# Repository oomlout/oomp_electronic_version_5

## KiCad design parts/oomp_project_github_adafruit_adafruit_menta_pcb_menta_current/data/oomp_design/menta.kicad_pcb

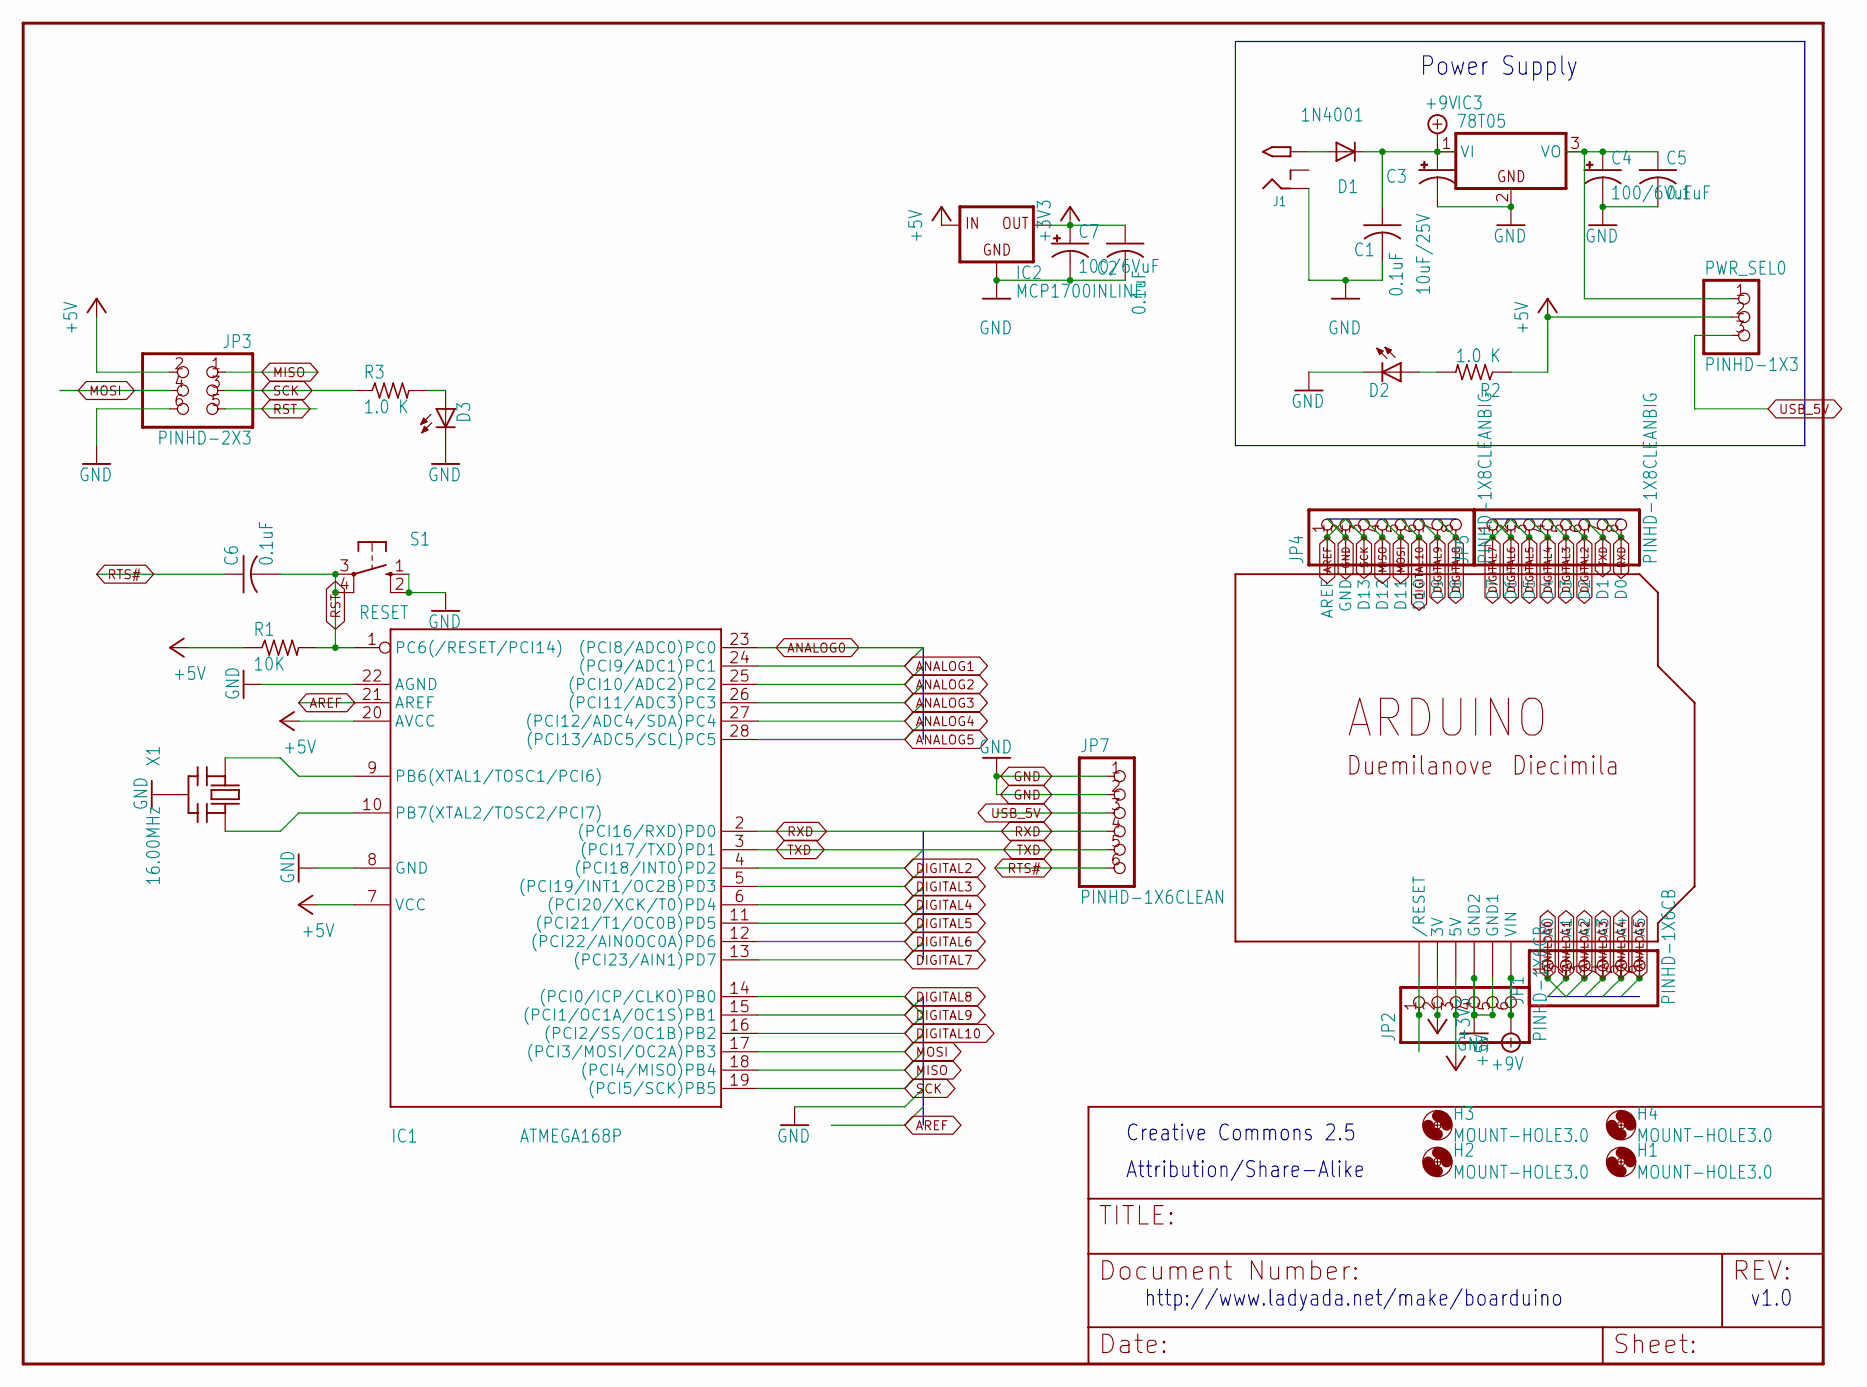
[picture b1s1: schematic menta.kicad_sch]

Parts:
C1, C2, C5, C6: 0.1uF; C025-025X050
C3: 10uF/25V; E2,5-6
C4, C7: 100/6VuF; E2,5-6
D1: 1N4001; DO41-10
D2: LED3MM
D3: Green; LED3MM
H1, H2, H3, H4: MOUNT-HOLE3.0; 3,0
IC1: ATMEGA168P; DIL28_3
IC2: MCP1700INLINE; TO92-INLINE
IC3: 78T05; TO220H
J1: 2.1MMJACK; PJ-102A
JP1, JP2: PINHD-1X6CB; 1X06-CLEANBIG
JP3: PINHD-2X3; 2X03
JP4, JP5: PINHD-1X8CLEANBIG; 1X08-CLEANBIG
JP7: PINHD-1X6CLEAN; 1X06-CLEAN
PWR_SEL0: PINHD-1X3; 1X03
R1: 10K; 0207_10
R2, R3: 1.0 K; 0207_10
S1: RESET; B3F-10XX
U$2: ARDUINO-NOHOLE
X1: 16.00MHz; CERM_OSC

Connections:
+3V3: C2.1, C7.+, IC2.3 (OUT), JP2.2, U$2.3V
+5V: IC1.7 (VCC), IC1.20 (AVCC), IC2.2 (IN), JP2.3, JP3.2, PWR_SEL0.2, R1.1, R2.1, U$2.5V
+9V: C1.1, C3.+, D1.C, IC3.1 (VI), JP2.6, U$2.VIN
ANALOG0: IC1.23 ((PCI8/ADC0)PC0), JP1.1, U$2.A0
ANALOG1: IC1.24 ((PCI9/ADC1)PC1), JP1.2, U$2.A1
ANALOG2: IC1.25 ((PCI10/ADC2)PC2), JP1.3, U$2.A2
ANALOG3: IC1.26 ((PCI11/ADC3)PC3), JP1.4, U$2.A3
ANALOG4: IC1.27 ((PCI12/ADC4/SDA)PC4), JP1.5, U$2.A4
ANALOG5: IC1.28 ((PCI13/ADC5/SCL)PC5), JP1.6, U$2.A5
AREF: IC1.21 (AREF), JP4.1, U$2.AREF
DIGITAL2: IC1.4 ((PCI18/INT0)PD2), JP5.6, U$2.D2
DIGITAL3: IC1.5 ((PCI19/INT1/OC2B)PD3), JP5.5, U$2.D3
DIGITAL4: IC1.6 ((PCI20/XCK/T0)PD4), JP5.4, U$2.D4
DIGITAL5: IC1.11 ((PCI21/T1/OC0B)PD5), JP5.3, U$2.D5
DIGITAL6: IC1.12 ((PCI22/AIN0OC0A)PD6), JP5.2, U$2.D6
DIGITAL7: IC1.13 ((PCI23/AIN1)PD7), JP5.1, U$2.D7
DIGITAL8: IC1.14 ((PCI0/ICP/CLKO)PB0), JP4.8, U$2.D8
DIGITAL9: IC1.15 ((PCI1/OC1A/OC1S)PB1), JP4.7, U$2.D9
DIGITAL10: IC1.16 ((PCI2/SS/OC1B)PB2), JP4.6, U$2.D10
GND: C1.2, C2.2, C3.-, C4.-, C5.2, C7.-, D2.K (C), D3.K (C), IC1.8 (GND), IC1.22 (AGND), IC2.1 (GND), IC3.2 (GND), J1.RING, JP2.4, JP2.5, JP3.6, JP4.2, JP7.1, JP7.2, S1.1 (S), S1.2 (S1), U$2.GND, U$2.GND1, U$2.GND2, X1.P$2 (GND)
MISO: IC1.18 ((PCI4/MISO)PB4), JP3.1, JP4.4, U$2.D12
MOSI: IC1.17 ((PCI3/MOSI/OC2A)PB3), JP3.4, JP4.5, U$2.D11
unnamed: IC1.9 (PB6(XTAL1/TOSC1/PCI6)), X1.P$1 (IN)
unnamed: IC1.10 (PB7(XTAL2/TOSC2/PCI7)), X1.P$3 (OUT)
unnamed: D2.A, R2.2
unnamed: D3.A, R3.2
unnamed: C4.+, C5.1, IC3.3 (VO), PWR_SEL0.1
unnamed: D1.A, J1.TIP
RTS#: C6.1, JP7.6
RXD: IC1.2 ((PCI16/RXD)PD0), JP5.8, JP7.4, U$2.D0
SCK: IC1.19 ((PCI5/SCK)PB5), JP3.3, JP4.3, R3.1, U$2.D13
TXD: IC1.3 ((PCI17/TXD)PD1), JP5.7, JP7.5, U$2.D1
USB_5V: JP7.3, PWR_SEL0.3

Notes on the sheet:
Power Supply
v1.0
http://www.ladyada.net/make/boarduino
Attribution/Share-Alike
Creative Commons 2.5

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
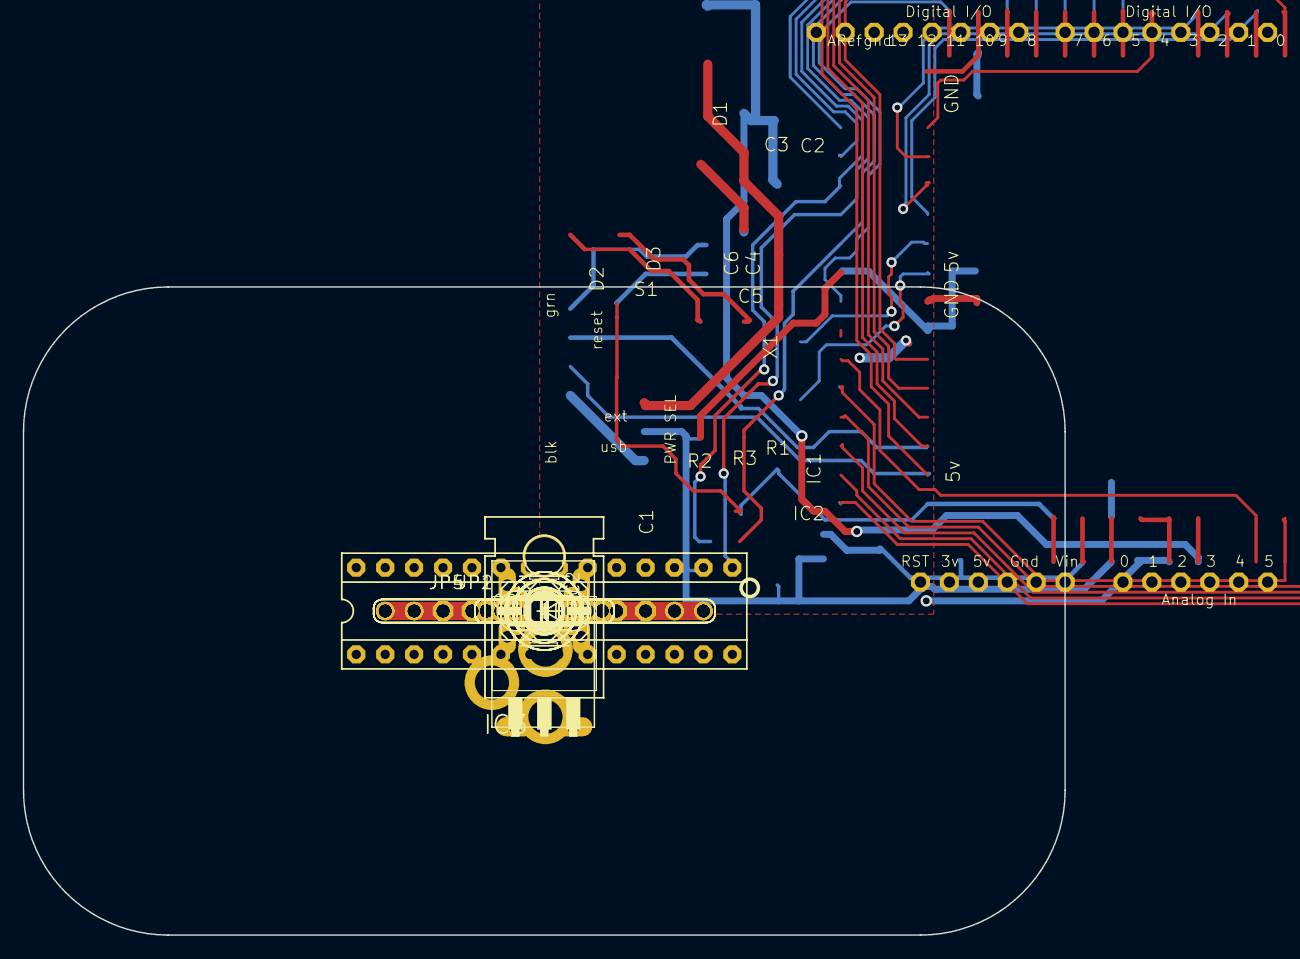
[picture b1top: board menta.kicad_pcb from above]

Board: 16 copper layers, 91.4 x 56.9 mm, 60 parts (1 on the bottom side), 34 nets.

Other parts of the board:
U$3, U$4, U$5, U$6: 12-STRIP
U$7, U$8, U$9, U$10, U$11, U$12, U$13, U$14, U$15, U$16, U$17, U$18, U$19, U$20, U$21, U$22, U$23, U$24, U$25, U$26, U$27, U$28, U$29, U$30: 5-STRIP
U$31: ALTOIDSTIN-DIM

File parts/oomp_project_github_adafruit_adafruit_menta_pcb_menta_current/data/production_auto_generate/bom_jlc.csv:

Comment,Designator,Footprint,LCSC Part #
,PWR_SEL0,menta-import-fps:1X03,C49257
,JP7,menta-import-fps:1X06-CLEAN,C37208
,"JP1,JP2",menta-import-fps:1X06-CLEANBIG,C37208
,"JP4,JP5",menta-import-fps:1X08-CLEANBIG,C492421
,JP3,menta-import-fps:2X03,
,U$31,menta-import-fps:ALTOIDSTIN-DIM,
,D2,menta-import-fps:LED3MM,
,IC2,menta-import-fps:TO92-INLINE,
0.1uF,"C1,C2,C5,C6",menta-import-fps:C025-025X050,
1.0 K,"R2,R3",menta-import-fps:0207_10,
100/6VuF,"C4,C7","menta-import-fps:E2,5-6",
10K,R1,menta-import-fps:0207_10,
10uF/25V,C3,"menta-import-fps:E2,5-6",
1N4001,D1,menta-import-fps:DO41-10,
2.1MMJACK,J1,menta-import-fps:PJ-102A,
7805T,IC3,menta-import-fps:TO220H,
ARDUINO-NOHOLE,U$2,menta-import-fps:ARDUINO-NOHOLE,
ATMEGA168P,IC1,menta-import-fps:DIL28_3,
Green,D3,menta-import-fps:LED3MM,
RESET,S1,menta-import-fps:B3F-10XX,

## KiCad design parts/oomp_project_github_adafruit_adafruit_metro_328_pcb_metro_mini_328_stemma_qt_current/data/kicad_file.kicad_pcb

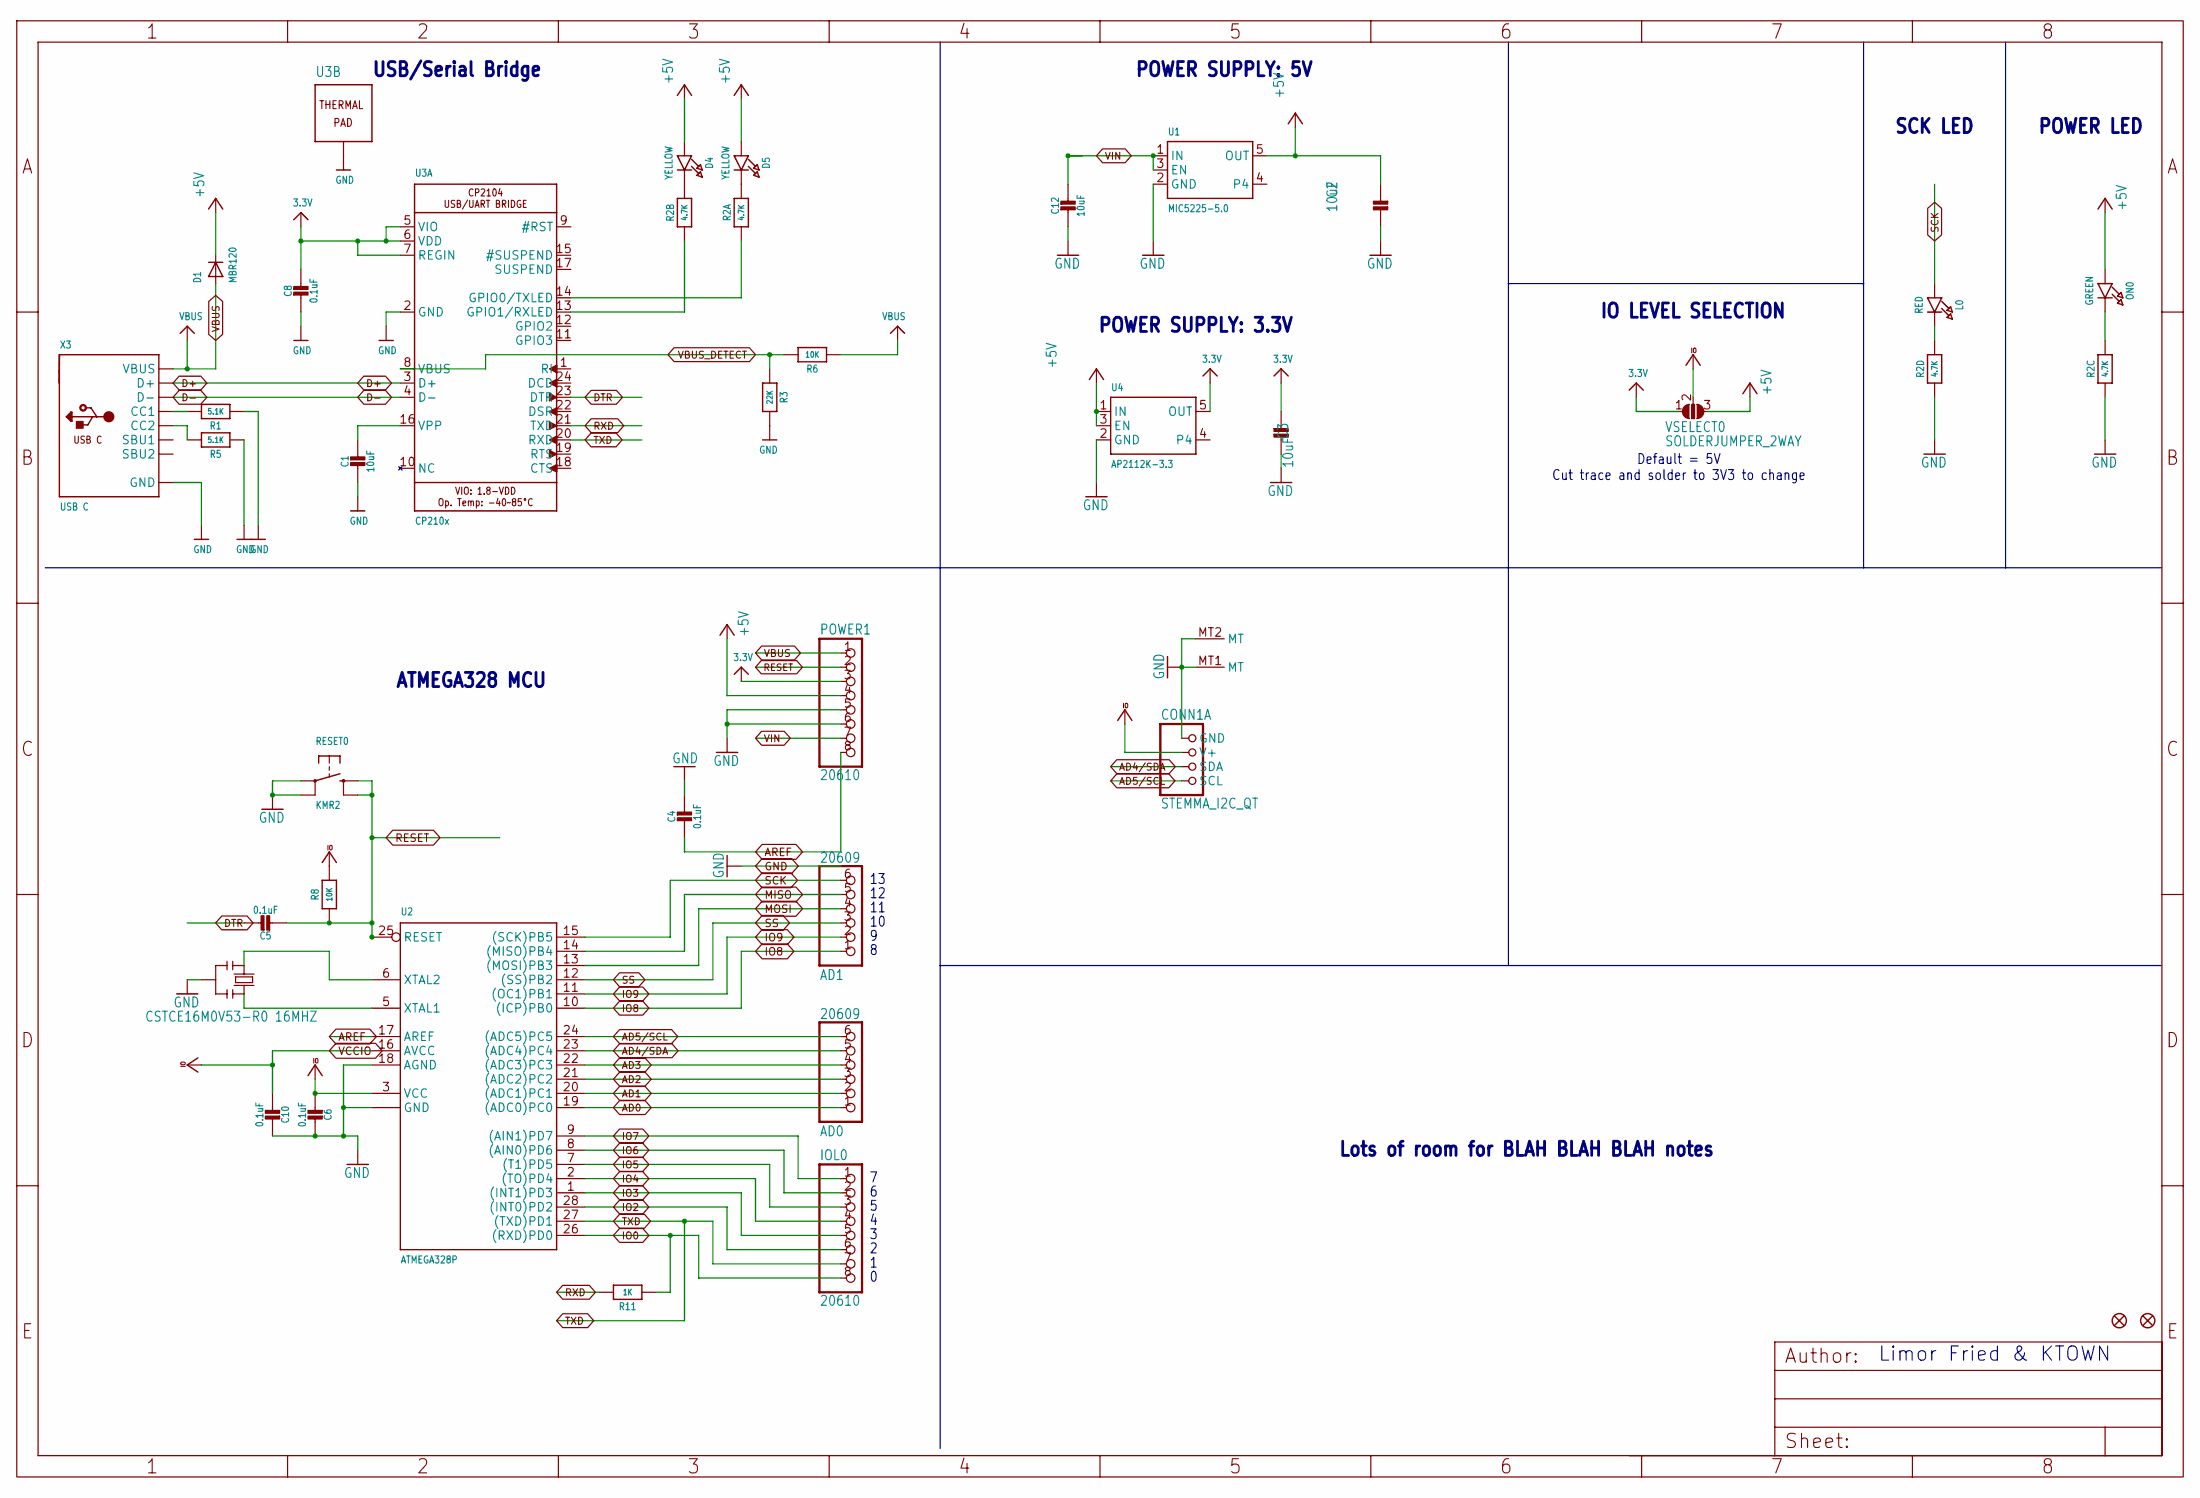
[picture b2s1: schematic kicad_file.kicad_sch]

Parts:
AD0, AD1: 20609; 1X06_ROUND
C1, C2, C3, C12: 10uF; 0805-NO
C4, C5, C6, C8, C10: 0.1uF; 0603-NO
CONN1: STEMMA_I2C_QT; JST_SH4
D1: MBR120; SOD-123FL
D4, D5: YELLOW; CHIPLED_0603_NOOUTLINE
FD1, FD2: FIDUCIAL_1MM
IOL0: 20610; 1X08_ROUND
L0: RED; CHIPLED_0603_NOOUTLINE
ON0: GREEN; CHIPLED_0603_NOOUTLINE
POWER1: 20610; 1X08_ROUND_70
R1, R5: 5.1K; 0603-NO
R2: 4.7K; RESPACK_4X0603
R3: 22K; 0603-NO
R6, R8: 10K; 0603-NO
R11: 1K; 0603-NO
RESET0: KMR2; BTN_KMR2_4.6X2.8
U1: MIC5225-5.0; SOT23-5
U2: ATMEGA328P; QFN28_4MM_.45MM
U3: CP210x; QFN24_4MM_SMSC
U4: AP2112K-3.3; SOT23-5
VSELECT0: SOLDERJUMPER_2WAY; SOLDERJUMPER_2WAY_OPEN_NOPASTE
X3: USB C; USB_C_CUSB31-CFM2AX-01-X
Y2: CSTCE16M0V53-R0 16MHZ; RESONATOR

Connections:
3.3V: C3.2, C8.1, POWER1.3, U3.5 (VIO), U3.6 (VDD), U3.7 (REGIN), U4.5 (OUT), VSELECT0.1
+5V: C2.2, D1.C, D4.A, D5.A, ON0.A, POWER1.4, U1.5 (OUT), U4.1 (IN), U4.3 (EN), VSELECT0.3
AD0: AD0.1, U2.19 ((ADC0)PC0)
AD1: AD0.2, U2.20 ((ADC1)PC1)
AD2: AD0.3, U2.21 ((ADC2)PC2)
AD3: AD0.4, U2.22 ((ADC3)PC3)
AD4/SDA: AD0.5, CONN1.3 (SDA), U2.23 ((ADC4)PC4)
AD5/SCL: AD0.6, CONN1.4 (SCL), U2.24 ((ADC5)PC5)
AREF: C4.2, POWER1.8, U2.17 (AREF)
D+: U3.3 (D+), X3.A6 (D+), X3.B6 (D+)
D-: U3.4 (D-), X3.A7 (D-), X3.B7 (D-)
DTR: C5.1, U3.23 (DTR)
GND: C1.2, C2.1, C3.1, C4.1, C6.1, C8.2, C10.1, C12.2, CONN1.1 (GND), CONN1.MT1 (MT), CONN1.MT2 (MT), POWER1.5, POWER1.6, R1.1, R2.3 (1), R2.4 (1), R3.1, R5.1, RESET0.A, RESET0.A' (P1), U1.2 (GND), U2.4 (GND), U2.18 (AGND), U2.29 (GND), U3.2 (GND), U3.THERM (TP), U4.2 (GND), X3.A1B12 (GND), X3.B1A12 (GND), Y2.2
IO0: IOL0.8, R11.1, U2.26 ((RXD)PD0)
IO2: IOL0.6, U2.28 ((INT0)PD2)
IO3: IOL0.5, U2.1 ((INT1)PD3)
IO4: IOL0.4, U2.2 ((TO)PD4)
IO5: IOL0.3, U2.7 ((T1)PD5)
IO6: IOL0.2, U2.8 ((AIN0)PD6)
IO7: IOL0.1, U2.9 ((AIN1)PD7)
IO8: AD1.1, U2.10 ((ICP)PB0)
IO9: AD1.2, U2.11 ((OC1)PB1)
MISO: AD1.5, U2.14 ((MISO)PB4)
MOSI: AD1.4, U2.13 ((MOSI)PB3)
unnamed: L0.C, R2.5 (2)
unnamed: ON0.C, R2.6 (2)
unnamed: R2.1, U3.14 (GPIO0/TXLED)
unnamed: R1.2, X3.A5 (CC1)
unnamed: D4.C, R2.7 (2)
unnamed: D5.C, R2.8 (2)
unnamed: R5.2, X3.B5 (CC2)
unnamed: C1.1, U3.16 (VPP)
unnamed: R2.2 (1), U3.13 (GPIO1/RXLED)
RESET: C5.2, POWER1.2, R8.1, RESET0.B (S), RESET0.B' (S1), U2.25 (RESET)
RXD: R11.2, U3.21 (TXD)
SCK: AD1.6, L0.A, U2.15 ((SCK)PB5)
SS: AD1.3, U2.12 ((SS)PB2)
TXD: IOL0.7, U2.27 ((TXD)PD1), U3.20 (RXD)
VBUS: D1.A, POWER1.1, R6.2, X3.A4B9 (VBUS), X3.B4A9 (VBUS)
VBUS_DETECT: R3.2, R6.1, U3.8 (VBUS)
VCCIO: C6.2, C10.2, CONN1.2 (V+), R8.2, U2.3 (VCC), U2.16 (AVCC), VSELECT0.2
VIN: C12.1, POWER1.7, U1.1 (IN), U1.3 (EN)
XTAL1: U2.5 (XTAL1), Y2.3
XTAL2: U2.6 (XTAL2), Y2.1

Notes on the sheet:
POWER SUPPLY: 5V
SCK LED
POWER LED
Lots of room for BLAH BLAH BLAH notes
Limor Fried & KTOWN
Default = 5V Cut trace and solder to 3V3 to change
USB/Serial Bridge
IO LEVEL SELECTION
ATMEGA328 MCU
POWER SUPPLY: 3.3V

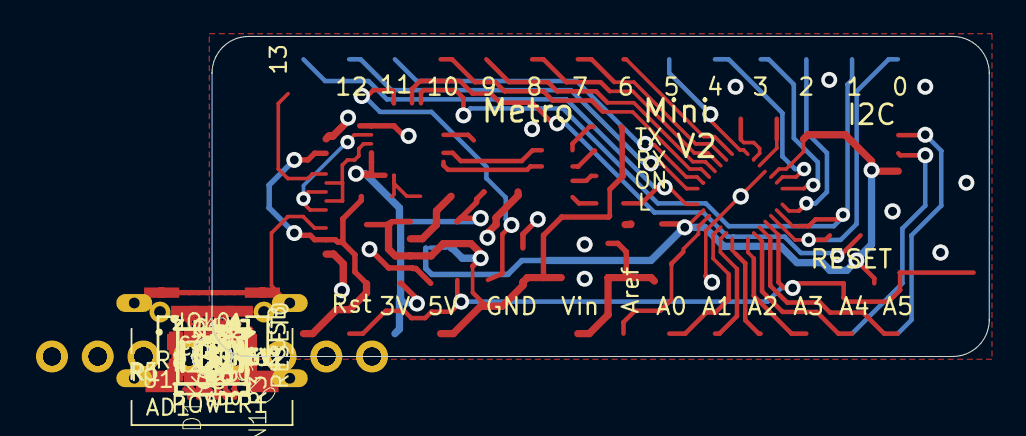
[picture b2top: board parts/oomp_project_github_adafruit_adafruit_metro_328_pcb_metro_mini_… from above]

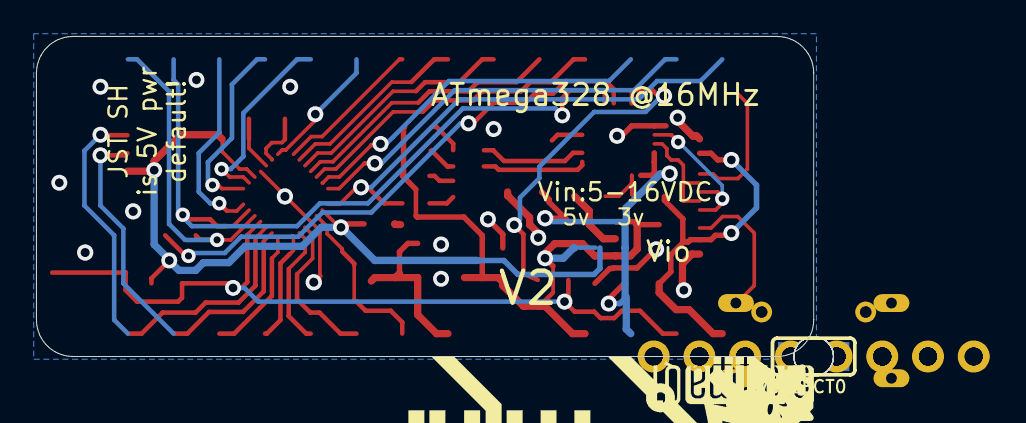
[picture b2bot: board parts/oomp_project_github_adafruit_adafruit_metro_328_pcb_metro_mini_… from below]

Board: 2 copper layers, 43.2 x 17.8 mm, 45 parts (4 on the bottom side), 44 nets.

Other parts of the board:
U$4: PCBFEAT-REV-040
U$5: ADAFRUIT_2.5MM
U$6: STEMMAQT
U$7: METROMINI_SILK
U$10: ADAFRUIT_5MM
UNK_HOLE_0: dummyfp0
UNK_HOLE_1: dummyfp1
UNK_HOLE_2: dummyfp2
UNK_HOLE_3: dummyfp3

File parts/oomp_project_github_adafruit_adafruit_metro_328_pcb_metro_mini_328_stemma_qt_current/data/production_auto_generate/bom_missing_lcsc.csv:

Designator,Comment,Footprint,OOMP ID,Reason
C1,10uF,Metro Mini 328 V2 - STEMMA QT-import-fps:0805-NO,electronic_capacitor_0805_10_micro_farad,No verified LCSC part number
C2,10uF,Metro Mini 328 V2 - STEMMA QT-import-fps:0805-NO,electronic_capacitor_0805_10_micro_farad,No verified LCSC part number
C3,10uF,Metro Mini 328 V2 - STEMMA QT-import-fps:0805-NO,electronic_capacitor_0805_10_micro_farad,No verified LCSC part number
C12,10uF,Metro Mini 328 V2 - STEMMA QT-import-fps:0805-NO,electronic_capacitor_0805_10_micro_farad,No verified LCSC part number
D1,MBR120,Metro Mini 328 V2 - STEMMA QT-import-fps:SOD-123FL,,No verified LCSC part number
D4,YELLOW,Metro Mini 328 V2 - STEMMA QT-import-fps:CHIPLED_0603_NOOUTLINE,electronic_led_0603_yellow,No verified LCSC part number
D5,YELLOW,Metro Mini 328 V2 - STEMMA QT-import-fps:CHIPLED_0603_NOOUTLINE,electronic_led_0603_yellow,No verified LCSC part number
FD1,FIDUCIAL_1MM,Metro Mini 328 V2 - STEMMA QT-import-fps:FIDUCIAL_1MM,,No verified LCSC part number
FD2,FIDUCIAL_1MM,Metro Mini 328 V2 - STEMMA QT-import-fps:FIDUCIAL_1MM,,No verified LCSC part number
L0,RED,Metro Mini 328 V2 - STEMMA QT-import-fps:CHIPLED_0603_NOOUTLINE,electronic_led_0603_red,No verified LCSC part number
ON0,GREEN,Metro Mini 328 V2 - STEMMA QT-import-fps:CHIPLED_0603_NOOUTLINE,electronic_led_0603_green,No verified LCSC part number
RESET0,KMR2,Metro Mini 328 V2 - STEMMA QT-import-fps:BTN_KMR2_4.6X2.8,,No verified LCSC part number
U1,MIC5225-5.0,Metro Mini 328 V2 - STEMMA QT-import-fps:SOT23-5,,No verified LCSC part number
U2,ATMEGA328P,Metro Mini 328 V2 - STEMMA QT-import-fps:QFN28_4MM_.45MM,,No verified LCSC part number
U3,CP210x,Metro Mini 328 V2 - STEMMA QT-import-fps:QFN24_4MM_SMSC,,No verified LCSC part number
U4,AP2112K-3.3,Metro Mini 328 V2 - STEMMA QT-import-fps:SOT23-5,electronic_ic_sot_23_5_power_management_linear_voltage_regulator_diodes_ap2112k_3_3,No verified LCSC part number
U$4,,Metro Mini 328 V2 - STEMMA QT-import-fps:PCBFEAT-REV-040,,No verified LCSC part number
U$5,,Metro Mini 328 V2 - STEMMA QT-import-fps:ADAFRUIT_2.5MM,,No verified LCSC part number
U$6,,Metro Mini 328 V2 - STEMMA QT-import-fps:STEMMAQT,,No verified LCSC part number
U$7,,Metro Mini 328 V2 - STEMMA QT-import-fps:METROMINI_SILK,,No verified LCSC part number
U$10,,Metro Mini 328 V2 - STEMMA QT-import-fps:ADAFRUIT_5MM,,No verified LCSC part number
VSELECT0,,Metro Mini 328 V2 - STEMMA QT-import-fps:SOLDERJUMPER_2WAY_OPEN_NOPASTE,,No verified LCSC part number
X3,USB C,Metro Mini 328 V2 - STEMMA QT-import-fps:USB_C_CUSB31-CFM2AX-01-X,,No verified LCSC part number
Y2,CSTCE16M0V53-R0 16MHZ,Metro Mini 328 V2 - STEMMA QT-import-fps:RESONATOR,,No verified LCSC part number

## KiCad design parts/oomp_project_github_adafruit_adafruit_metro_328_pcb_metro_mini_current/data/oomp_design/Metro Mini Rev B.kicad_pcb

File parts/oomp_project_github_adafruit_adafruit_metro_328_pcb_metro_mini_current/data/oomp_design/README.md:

# OOMP KiCad design copy

Open `Metro Mini Rev B.kicad_pro` (or the `.kicad_pcb` / `.kicad_sch`) in KiCad. Local OOMP libraries are under `libraries/`. Original inputs are preserved in [../original/](../original/).

Only verified unchanged installed KiCad defaults were renamed. Modified, custom, unmatched and unavailable items remain unchanged. Soldering variants are never swapped during conversion. Existing pad coordinates, nets and UUIDs are preserved.

See [conversion_report.yaml](conversion_report.yaml) for every conversion and skip. Copy this directory before editing; regeneration refuses to overwrite edited design files.

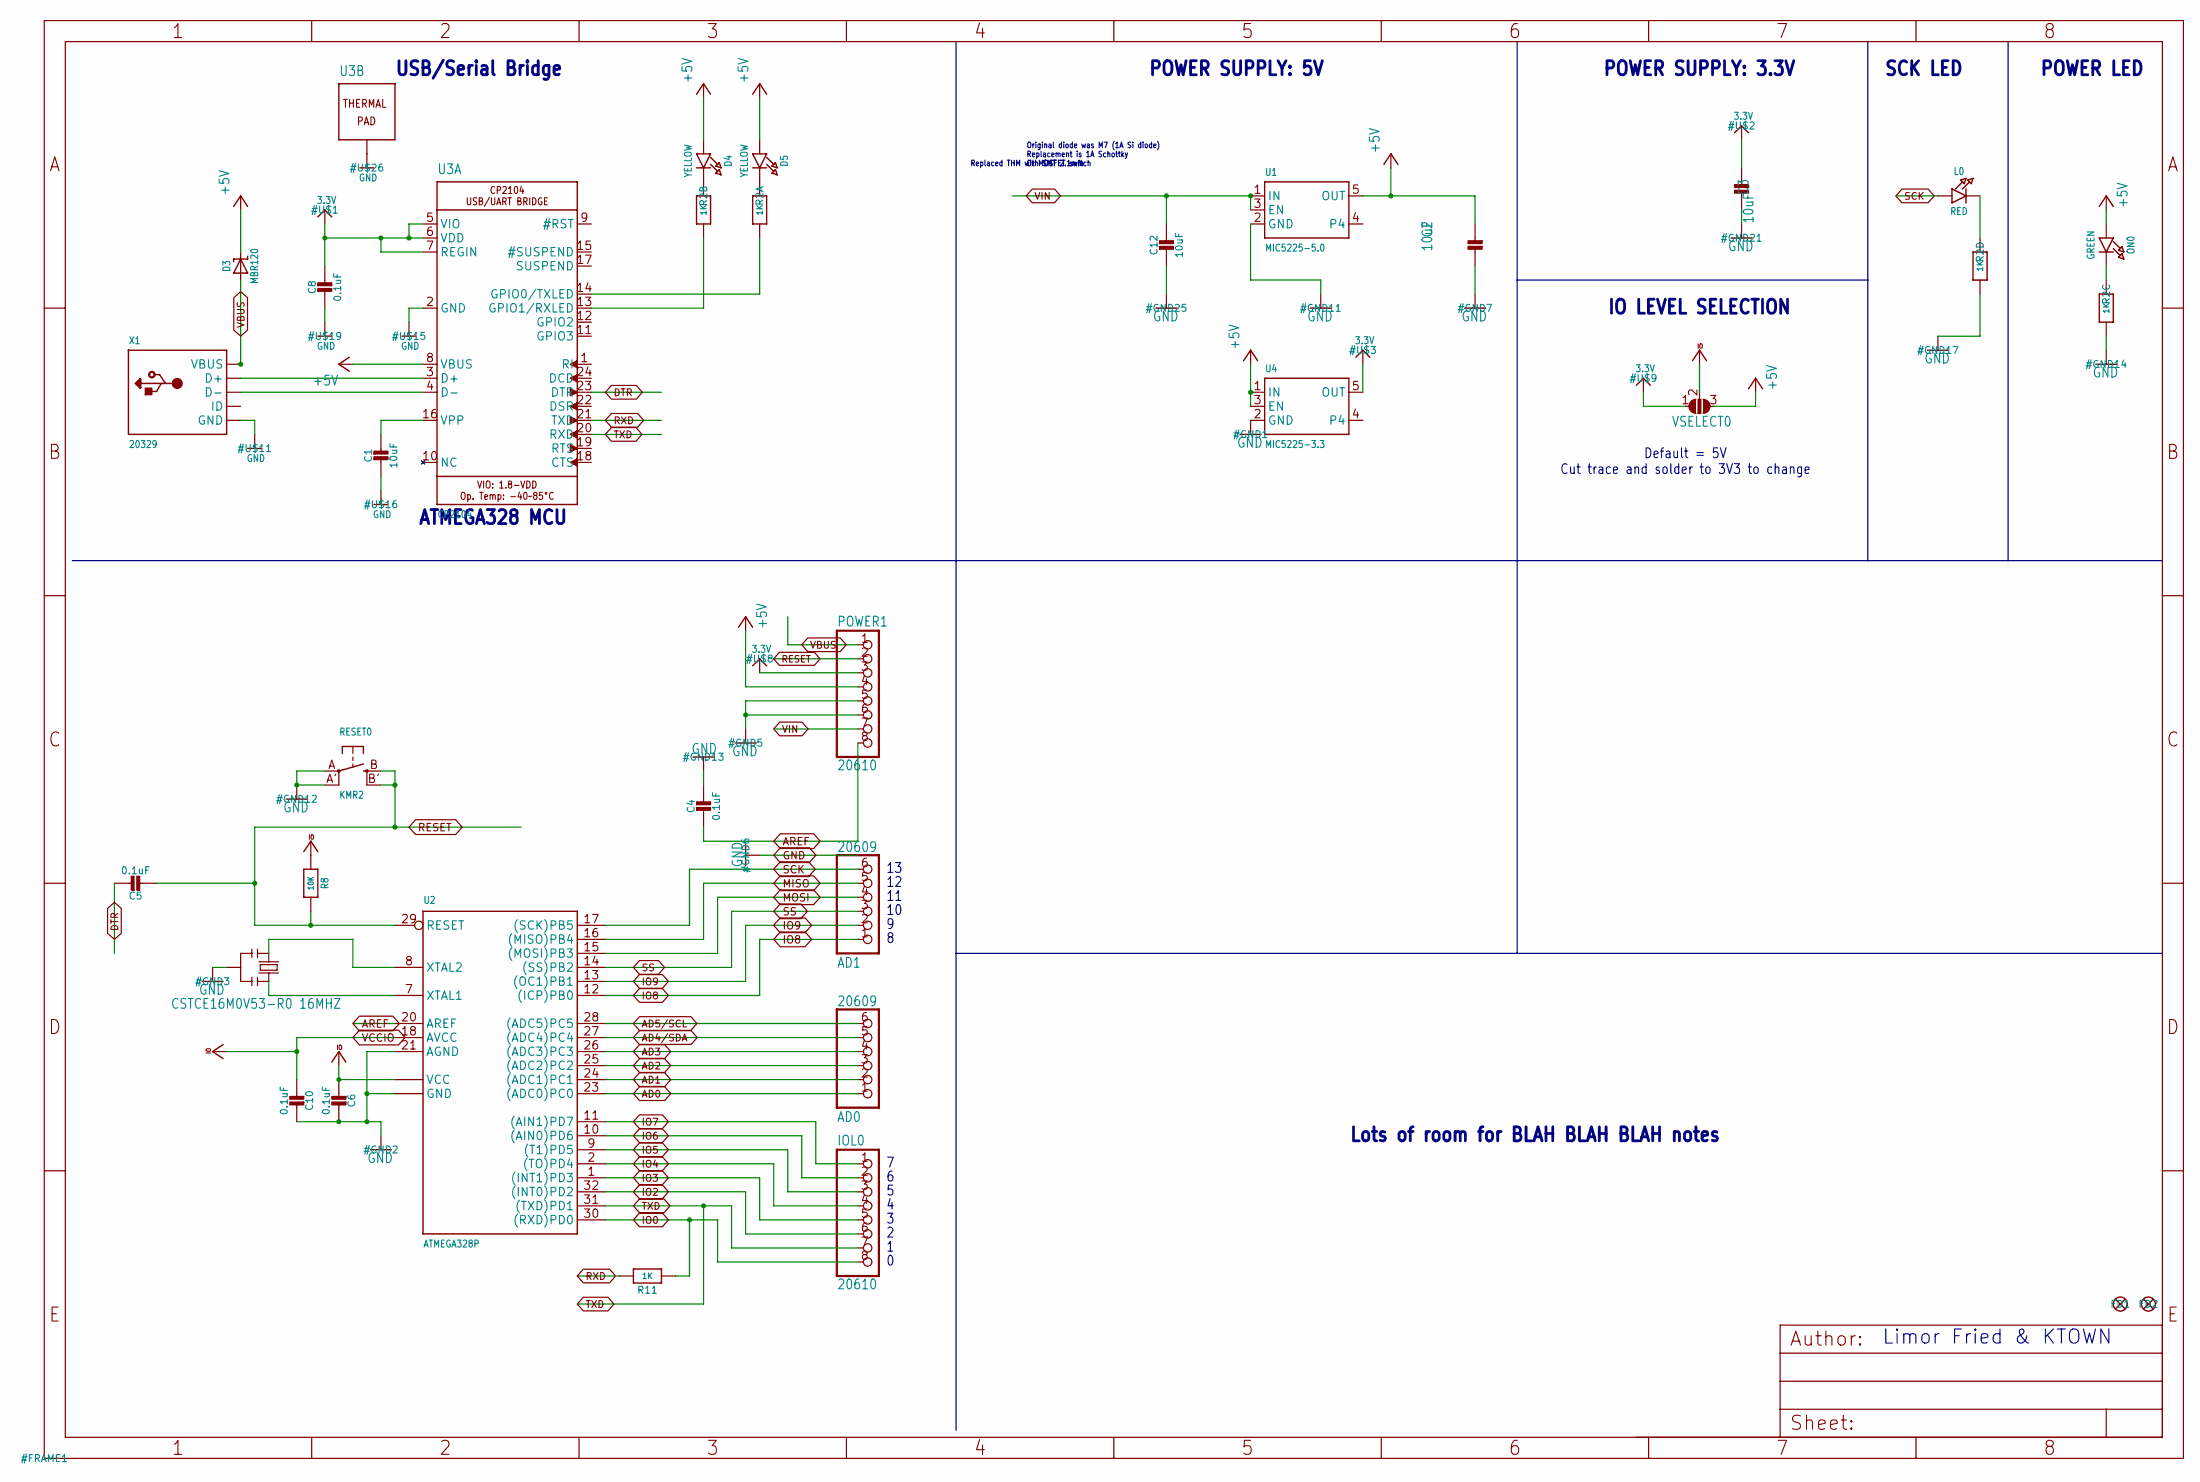
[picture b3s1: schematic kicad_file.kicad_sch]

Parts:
AD0, AD1: 20609; 1X06_ROUND
C1, C2, C3, C12: 10uF; 0805-NO
C4, C6, C8, C10: 0.1uF; 0805-NO
C5: 0.1uF; _0805MP
D3: MBR120; SOD-123
D4, D5: YELLOW; CHIPLED_0805_NOOUTLINE
FD1, FD2: FIDUCIAL""; FIDUCIAL_1MM
IOL0: 20610; 1X08_ROUND
L0: RED; CHIPLED_0805_NOOUTLINE
ON0: GREEN; CHIPLED_0805_NOOUTLINE
POWER1: 20610; 1X08_ROUND_70
R2: 1K; RESPACK_4X0603
R8: 10K; 0805-NO
R11: 1K; 0805-NO
RESET0: KMR2; BTN_KMR2_4.6X2.8
U1: MIC5225-5.0; SOT23-5
U2: ATMEGA328P; MLF32-TH
U3: CP2104; QFN24_4MM_SMSC
U4: MIC5225-3.3; SOT23-5
VSELECT0: SOLDERJUMPER_2WAY; SOLDERJUMPER_2WAY_OPEN_NOPASTE
X1: 20329; 4UCONN_20329_V2
Y2: CSTCE16M0V53-R0 16MHZ; RESONATOR

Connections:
3.3V: C3.2, C8.1, POWER1.3, U3.5 (VIO), U3.6 (VDD), U3.7 (REGIN), U4.5 (OUT), VSELECT0.1
+5V: C2.2, D3.C, D4.A, D5.A, ON0.A, POWER1.4, U1.5 (OUT), U3.8 (VBUS), U4.1 (IN), U4.3 (EN), VSELECT0.3
AD0: AD0.1, U2.23 ((ADC0)PC0)
AD1: AD0.2, U2.24 ((ADC1)PC1)
AD2: AD0.3, U2.25 ((ADC2)PC2)
AD3: AD0.4, U2.26 ((ADC3)PC3)
AD4/SDA: AD0.5, U2.27 ((ADC4)PC4)
AD5/SCL: AD0.6, U2.28 ((ADC5)PC5)
AREF: C4.2, POWER1.8, U2.20 (AREF)
DTR: C5.1, U3.23 (DTR)
GND: C1.2, C2.1, C3.1, C4.1, C6.1, C8.2, C10.1, C12.2, POWER1.5, POWER1.6, R2.3 (1), R2.4 (1), RESET0.A, RESET0.A' (P1), U1.2 (GND), U2.3 (GND), U2.5 (GND), U2.21 (AGND), U2.TH (GND), U3.2 (GND), U3.THERM (TP), U4.2 (GND), X1.BASE@1 (GND), X1.BASE@2 (GND), X1.GND, X1.SPRT@1 (GND), X1.SPRT@2 (GND), X1.SPRT@3 (GND), X1.SPRT@4 (GND), Y2.2
IO0: IOL0.8, R11.1, U2.30 ((RXD)PD0)
IO2: IOL0.6, U2.32 ((INT0)PD2)
IO3: IOL0.5, U2.1 ((INT1)PD3)
IO4: IOL0.4, U2.2 ((TO)PD4)
IO5: IOL0.3, U2.9 ((T1)PD5)
IO6: IOL0.2, U2.10 ((AIN0)PD6)
IO7: IOL0.1, U2.11 ((AIN1)PD7)
IO8: AD1.1, U2.12 ((ICP)PB0)
IO9: AD1.2, U2.13 ((OC1)PB1)
MISO: AD1.5, U2.16 ((MISO)PB4)
MOSI: AD1.4, U2.15 ((MOSI)PB3)
unnamed: L0.C, R2.5 (2)
unnamed: ON0.C, R2.6 (2)
unnamed: R2.1, U3.14 (GPIO0/TXLED)
unnamed: D4.C, R2.7 (2)
unnamed: D5.C, R2.8 (2)
unnamed: U3.3 (D+), X1.D+
unnamed: U3.4 (D-), X1.D-
unnamed: C1.1, U3.16 (VPP)
unnamed: R2.2 (1), U3.13 (GPIO1/RXLED)
RESET: C5.2, POWER1.2, R8.1, RESET0.B (S), RESET0.B' (S1), U2.29 (RESET)
RXD: R11.2, U3.21 (TXD)
SCK: AD1.6, L0.A, U2.17 ((SCK)PB5)
SS: AD1.3, U2.14 ((SS)PB2)
TXD: IOL0.7, U2.31 ((TXD)PD1), U3.20 (RXD)
VBUS: D3.A, POWER1.1, X1.VBUS
VCCIO: C6.2, C10.2, R8.2, U2.4 (VCC), U2.6 (VCC), U2.18 (AVCC), VSELECT0.2
VIN: C12.1, POWER1.7, U1.1 (IN), U1.3 (EN)
XTAL1: U2.7 (XTAL1), Y2.3
XTAL2: U2.8 (XTAL2), Y2.1

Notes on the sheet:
Limor Fried & KTOWN
Original diode was M7 (1A Si diode) Replacement is 1A Schottky Or MOSFET switch
USB/Serial Bridge
Default = 5V Cut trace and solder to 3V3 to change
POWER SUPPLY: 3.3V
POWER LED
Lots of room for BLAH BLAH BLAH notes
Replaced THM with SMT 2.1mm
IO LEVEL SELECTION
POWER SUPPLY: 5V
ATMEGA328 MCU
SCK LED

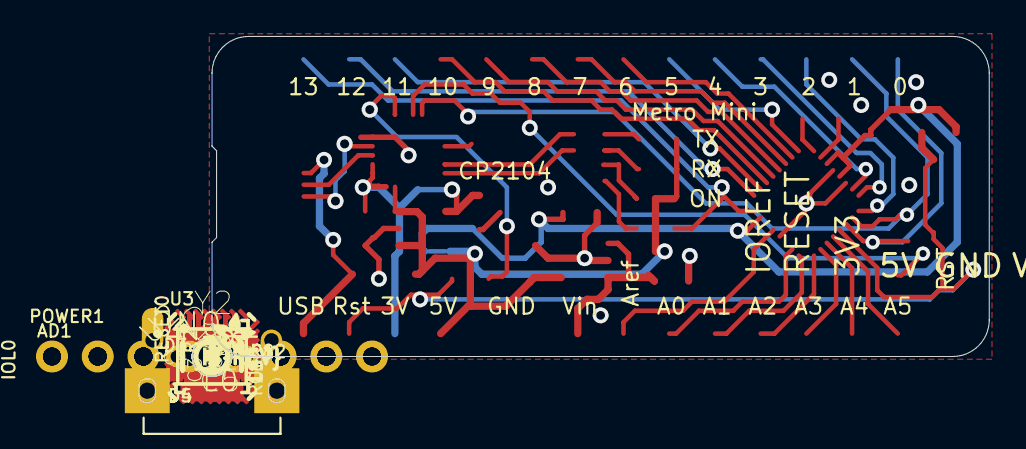
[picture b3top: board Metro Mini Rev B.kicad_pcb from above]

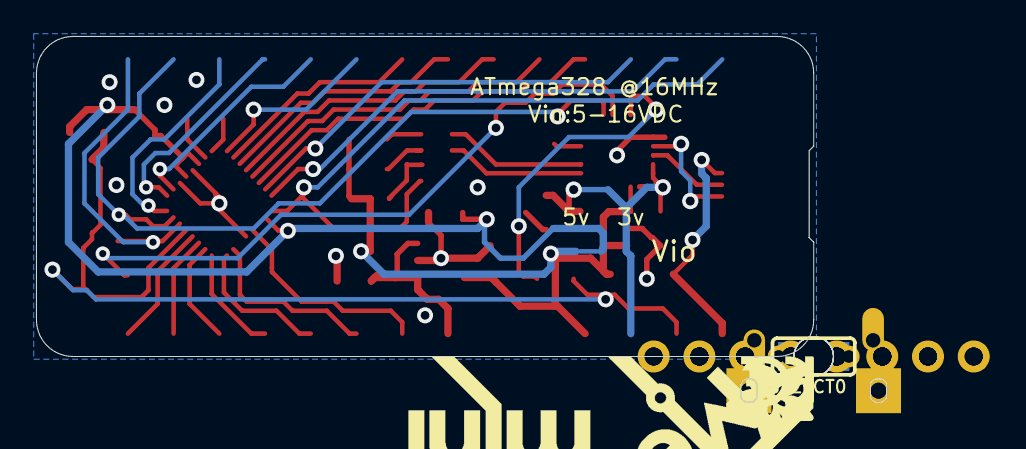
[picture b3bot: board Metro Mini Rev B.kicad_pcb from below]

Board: 2 copper layers, 43.2 x 17.8 mm, 41 parts (5 on the bottom side), 41 nets.

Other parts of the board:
U$4: PCBFEAT-REV-040
U$5: ADAFRUIT_2.5MM
U$7: METROMINI_SILK
U$10: ADAFRUIT_5MM
U$12: SYMBOL_CE_TINY
U$14: SYMBOL_FCC_TINY
UNK_HOLE_0: dummyfp0
UNK_HOLE_1: dummyfp1
UNK_HOLE_2: dummyfp2
UNK_HOLE_3: dummyfp3

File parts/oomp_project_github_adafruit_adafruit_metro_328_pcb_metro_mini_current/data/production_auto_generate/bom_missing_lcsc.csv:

Designator,Comment,Footprint,OOMP ID,Reason
C1,10uF,Metro Mini Rev B-import-fps:0805-NO,electronic_capacitor_0805_10_micro_farad,No verified LCSC part number
C2,10uF,Metro Mini Rev B-import-fps:0805-NO,electronic_capacitor_0805_10_micro_farad,No verified LCSC part number
C3,10uF,Metro Mini Rev B-import-fps:0805-NO,electronic_capacitor_0805_10_micro_farad,No verified LCSC part number
C4,0.1uF,Metro Mini Rev B-import-fps:0805-NO,,No verified LCSC part number
C5,0.1uF,Metro Mini Rev B-import-fps:_0805MP,,No verified LCSC part number
C6,0.1uF,Metro Mini Rev B-import-fps:0805-NO,,No verified LCSC part number
C8,0.1uF,Metro Mini Rev B-import-fps:0805-NO,,No verified LCSC part number
C10,0.1uF,Metro Mini Rev B-import-fps:0805-NO,,No verified LCSC part number
C12,10uF,Metro Mini Rev B-import-fps:0805-NO,electronic_capacitor_0805_10_micro_farad,No verified LCSC part number
D3,MBR120,Metro Mini Rev B-import-fps:SOD-123,,No verified LCSC part number
D4,YELLOW,Metro Mini Rev B-import-fps:CHIPLED_0805_NOOUTLINE,electronic_led_0805_yellow,No verified LCSC part number
D5,YELLOW,Metro Mini Rev B-import-fps:CHIPLED_0805_NOOUTLINE,electronic_led_0805_yellow,No verified LCSC part number
FD1,"FIDUCIAL""""",Metro Mini Rev B-import-fps:FIDUCIAL_1MM,,No verified LCSC part number
FD2,"FIDUCIAL""""",Metro Mini Rev B-import-fps:FIDUCIAL_1MM,,No verified LCSC part number
L0,RED,Metro Mini Rev B-import-fps:CHIPLED_0805_NOOUTLINE,electronic_led_0805_red,No verified LCSC part number
ON0,GREEN,Metro Mini Rev B-import-fps:CHIPLED_0805_NOOUTLINE,electronic_led_0805_green,No verified LCSC part number
RESET0,KMR2,Metro Mini Rev B-import-fps:BTN_KMR2_4.6X2.8,,No verified LCSC part number
U1,MIC5225-5.0,Metro Mini Rev B-import-fps:SOT23-5,,No verified LCSC part number
U2,ATMEGA328P,Metro Mini Rev B-import-fps:MLF32-TH,,No verified LCSC part number
U3,CP2104,Metro Mini Rev B-import-fps:QFN24_4MM_SMSC,,No verified LCSC part number
U4,MIC5225-3.3,Metro Mini Rev B-import-fps:SOT23-5,,No verified LCSC part number
U$4,,Metro Mini Rev B-import-fps:PCBFEAT-REV-040,,No verified LCSC part number
U$5,,Metro Mini Rev B-import-fps:ADAFRUIT_2.5MM,,No verified LCSC part number
U$7,,Metro Mini Rev B-import-fps:METROMINI_SILK,,No verified LCSC part number
U$10,,Metro Mini Rev B-import-fps:ADAFRUIT_5MM,,No verified LCSC part number
U$12,,Metro Mini Rev B-import-fps:SYMBOL_CE_TINY,,No verified LCSC part number
U$14,,Metro Mini Rev B-import-fps:SYMBOL_FCC_TINY,,No verified LCSC part number
VSELECT0,,Metro Mini Rev B-import-fps:SOLDERJUMPER_2WAY_OPEN_NOPASTE,,No verified LCSC part number
X1,20329,Metro Mini Rev B-import-fps:4UCONN_20329_V2,,No verified LCSC part number
Y2,CSTCE16M0V53-R0 16MHZ,Metro Mini Rev B-import-fps:RESONATOR,,No verified LCSC part number
